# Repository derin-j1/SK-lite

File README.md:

# SK-lite
A door sensor with a nano,buzzer,magnetic switch,oled screen and a custom made pcb.can be used to check if door is open or not and check how mant times it opens

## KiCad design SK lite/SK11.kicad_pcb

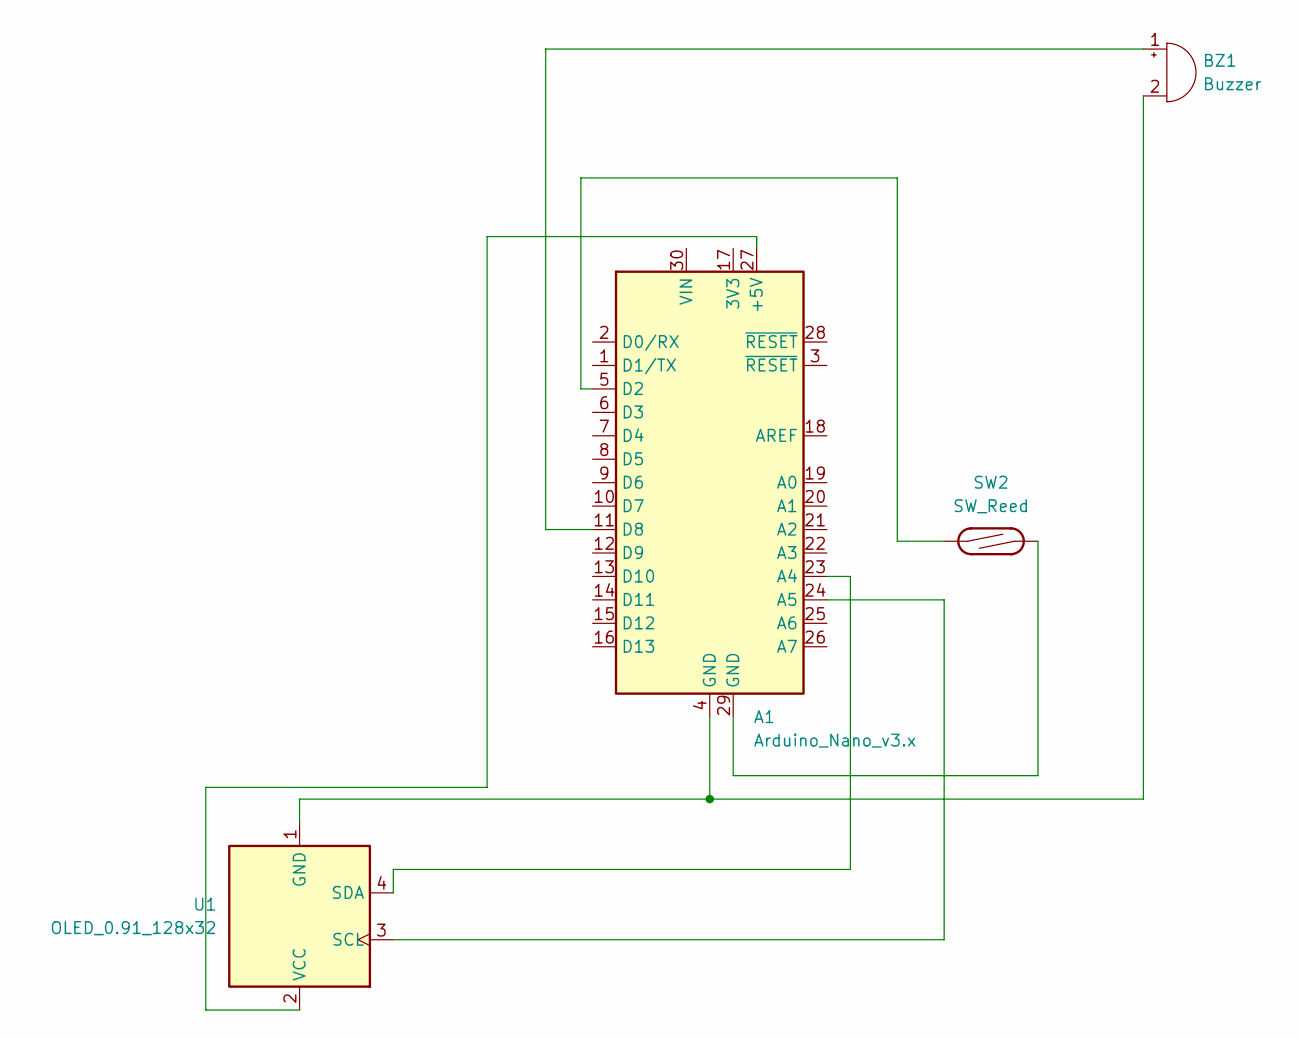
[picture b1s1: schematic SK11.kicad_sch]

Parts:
A1: Arduino_Nano_v3.x; Arduino_Nano
BZ1: Buzzer; Buzzer_12x9.5RM7.6
SW2: SW_Reed; PinHeader_1x02_P1.00mm_Horizontal
U1: OLED_0.91_128x32

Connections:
unnamed: A1.27 (+5V), U1.2 (VCC)
unnamed: A1.23 (A4), U1.4 (SDA)
unnamed: A1.24 (A5), U1.3 (SCL)
unnamed: A1.5 (D2), SW2.1
unnamed: A1.11 (D8), BZ1.1 (+)
unnamed: A1.29 (GND), SW2.2
unnamed: A1.4 (GND), BZ1.2 (-), U1.1 (GND)

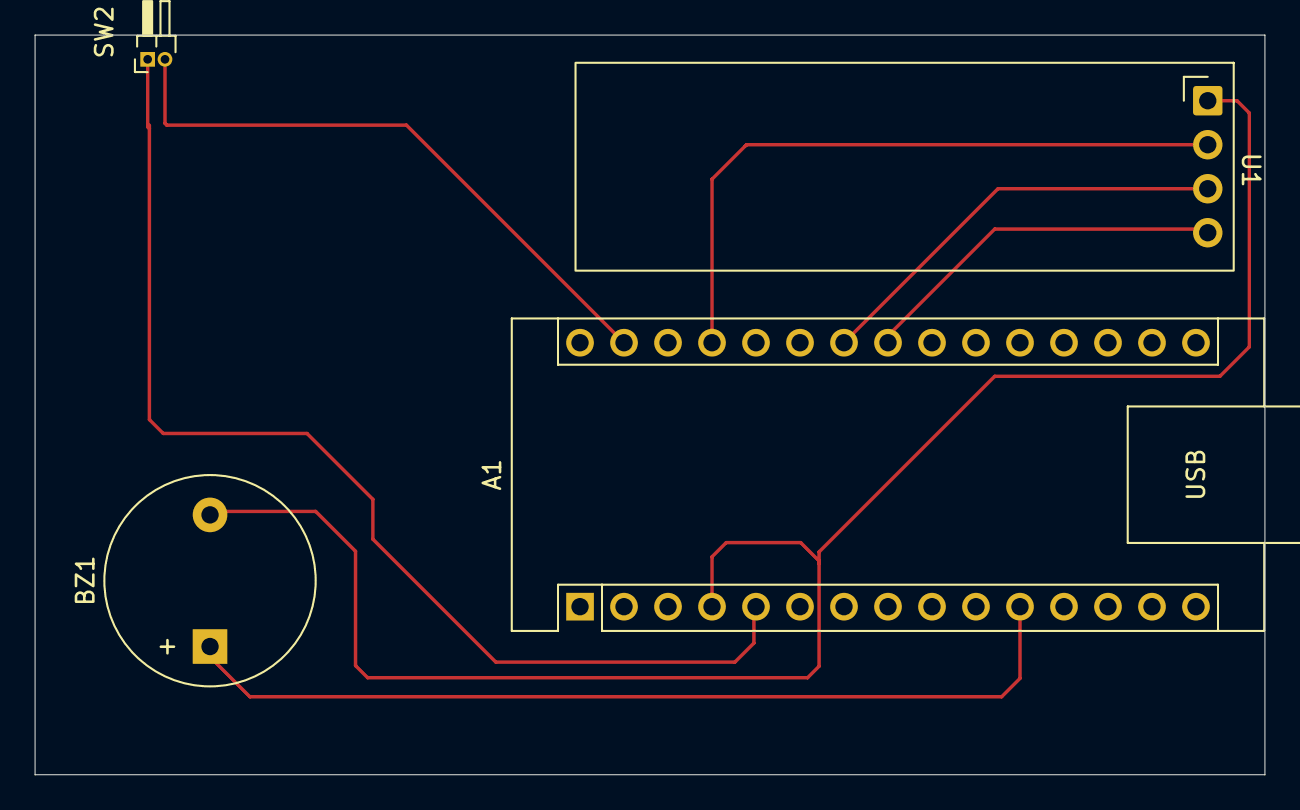
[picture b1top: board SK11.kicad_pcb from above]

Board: 2 copper layers, 71.0 x 42.7 mm, 4 parts (0 on the bottom side), 7 nets.
